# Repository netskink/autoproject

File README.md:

autoproject
===========

arduino code for triple gauge I built using arduino.
My youtube channel uploads have videos used during construction
and the final results.

http://www.youtube.com/user/netskink/videos

I gave a presentation on this project at FOSS in Raleigh and at DefCon in Las Vegas for HHV.
Here is one version of it.
https://docs.google.com/presentation/d/1aC9Kk9lGGvgu6jle9UMkTmX3eTjt8OQHqn5Oco8srgs/edit?usp=sharing

John

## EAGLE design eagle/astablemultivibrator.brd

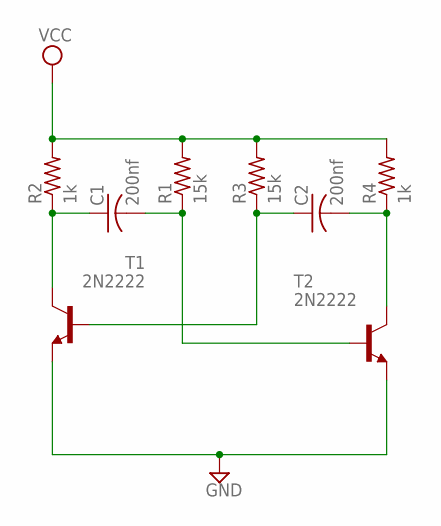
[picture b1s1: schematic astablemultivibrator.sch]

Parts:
C1, C2: 200nf; C025-030X050
R1, R3: 15k; 0309/12
R2, R4: 1k; 0309/12
T1, T2: 2N2222; TO92-EBC-OVAL

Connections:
GND: T1.E, T2.E
unnamed: C1.1, R2.1, T1.C
unnamed: C1.2, R1.1, T2.B
unnamed: C2.1, R3.1, T1.B
unnamed: C2.2, R4.1, T2.C
VCC: R1.2, R2.2, R3.2, R4.2

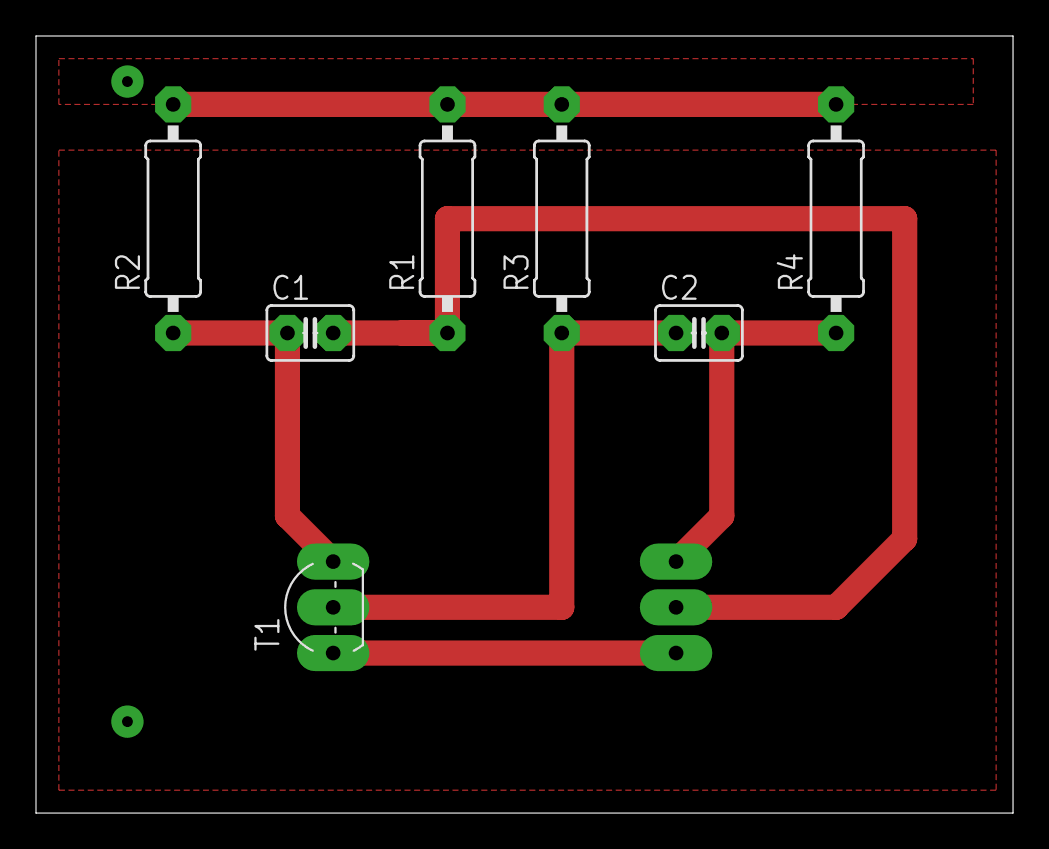
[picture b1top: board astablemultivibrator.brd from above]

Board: 2 copper layers, 54.3 x 43.2 mm, 8 parts (1 on the bottom side), 6 nets.

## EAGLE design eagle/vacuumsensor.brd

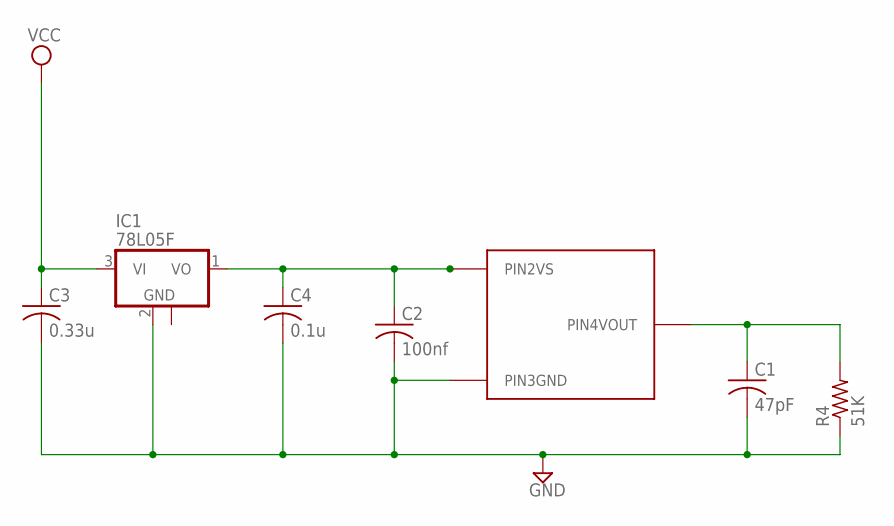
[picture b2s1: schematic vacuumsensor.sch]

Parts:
C1: 47pF; C050-024X044
C2: 100nf; C050-024X044
C3: 0.33u; C050-024X044
C4: 0.1u; C050-024X044
IC1: 78L05F; SOT89
R4: 51K; 0309/12
U$1: MPXV6115V6U; 482A

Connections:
GND: C1.2, C2.2, C3.2, C4.2, IC1.2 (GND), R4.1, U$1.P$3 (PIN3GND)
unnamed: C1.1, R4.2, U$1.P$4 (PIN4VOUT)
unnamed: C2.1, C4.1, IC1.1 (VO), U$1.P$2 (PIN2VS)
VCC: C3.1, IC1.3 (VI)

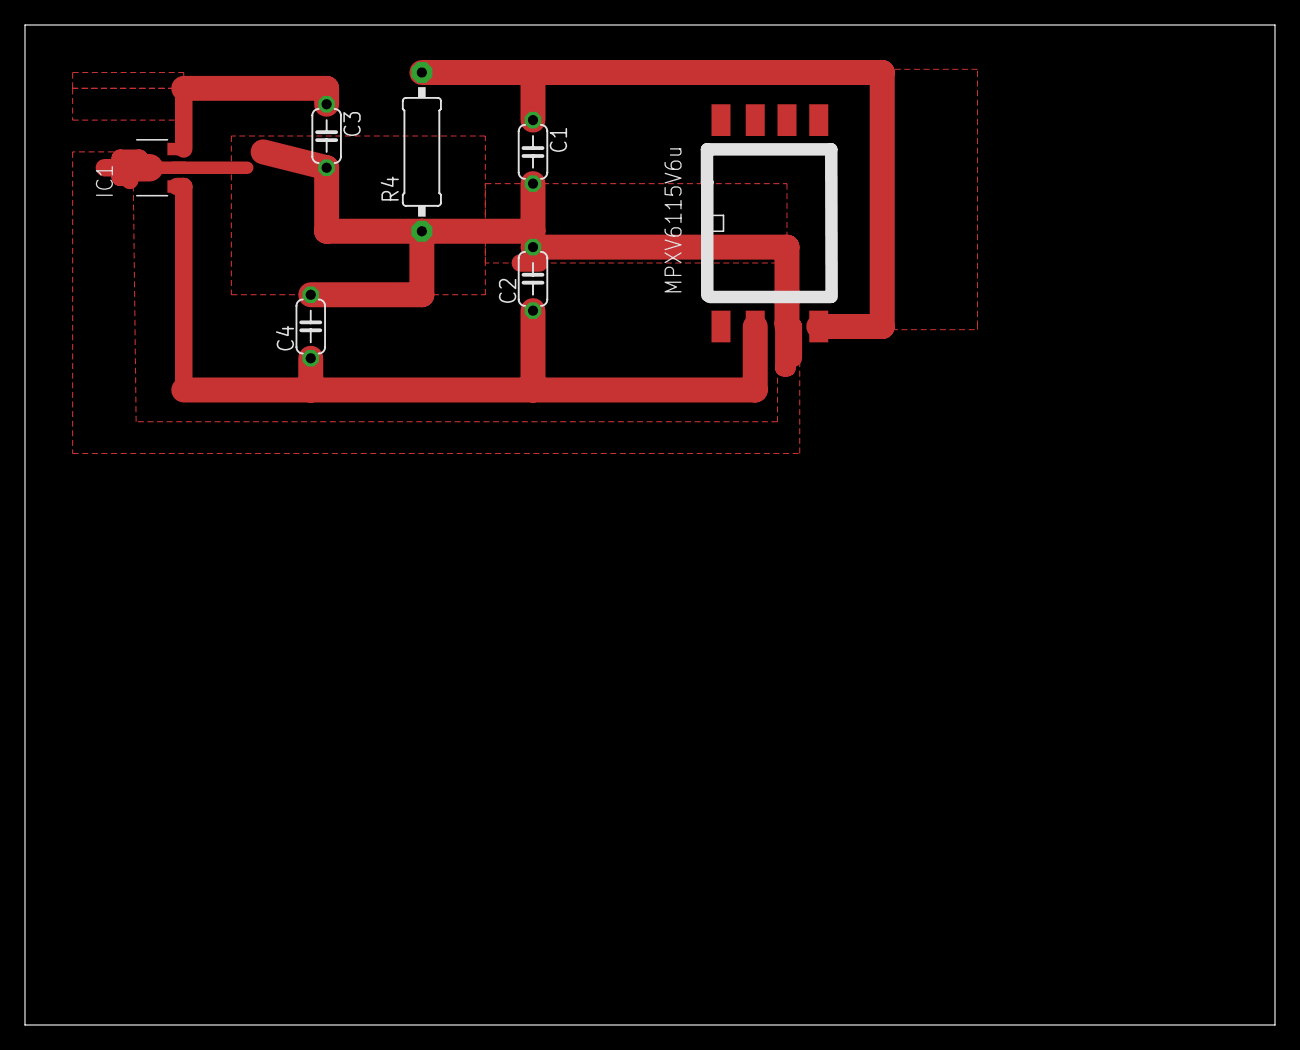
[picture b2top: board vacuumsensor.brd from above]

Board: 2 copper layers, 100.0 x 80.0 mm, 7 parts (0 on the bottom side), 4 nets.

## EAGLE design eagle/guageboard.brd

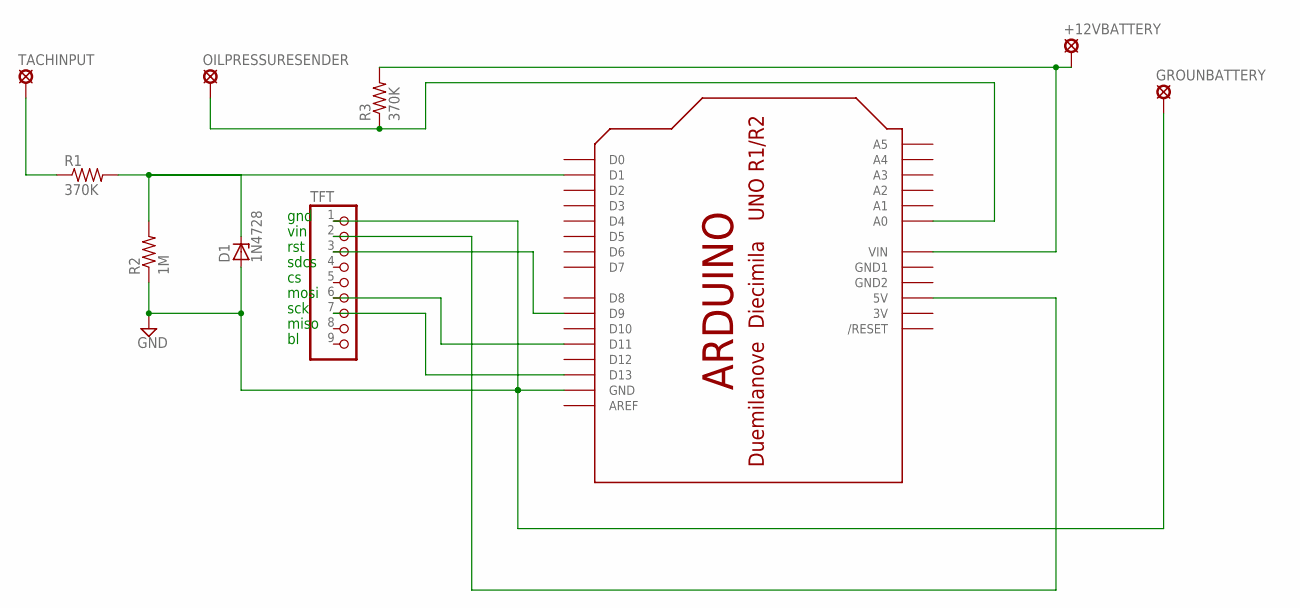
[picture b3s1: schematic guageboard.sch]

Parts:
+12VBATTERY: MCS10B
D1: 1N4728; DO41Z10
GROUNBATTERY: MCS10B
OILPRESSURESENDER: MCS10B
R1, R3: 370K; 0204/5
R2: 1M; 0204/5
TACHINPUT: MCS10B
TFT: PINHD-1X9; 1X09-BIG
U$1: ARDUINOUNO; ARDUINO

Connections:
3V: U$1.3V
5V: TFT.2, U$1.5V
GND: D1.A, GROUNBATTERY.MP, R2.1, TFT.1, U$1.GND, U$1.GND2
GND1: U$1.GND1
unnamed: D1.C, R1.2, R2.2, U$1.D1
unnamed: R1.1, TACHINPUT.MP
unnamed: OILPRESSURESENDER.MP, R3.1, U$1.A0
unnamed: TFT.7, U$1.D13
unnamed: TFT.6, U$1.D11
unnamed: TFT.3, U$1.D9
VIN: +12VBATTERY.MP, R3.2, U$1.VIN

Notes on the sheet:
gnd
vin
rst
sdcs
mosi
sck
miso

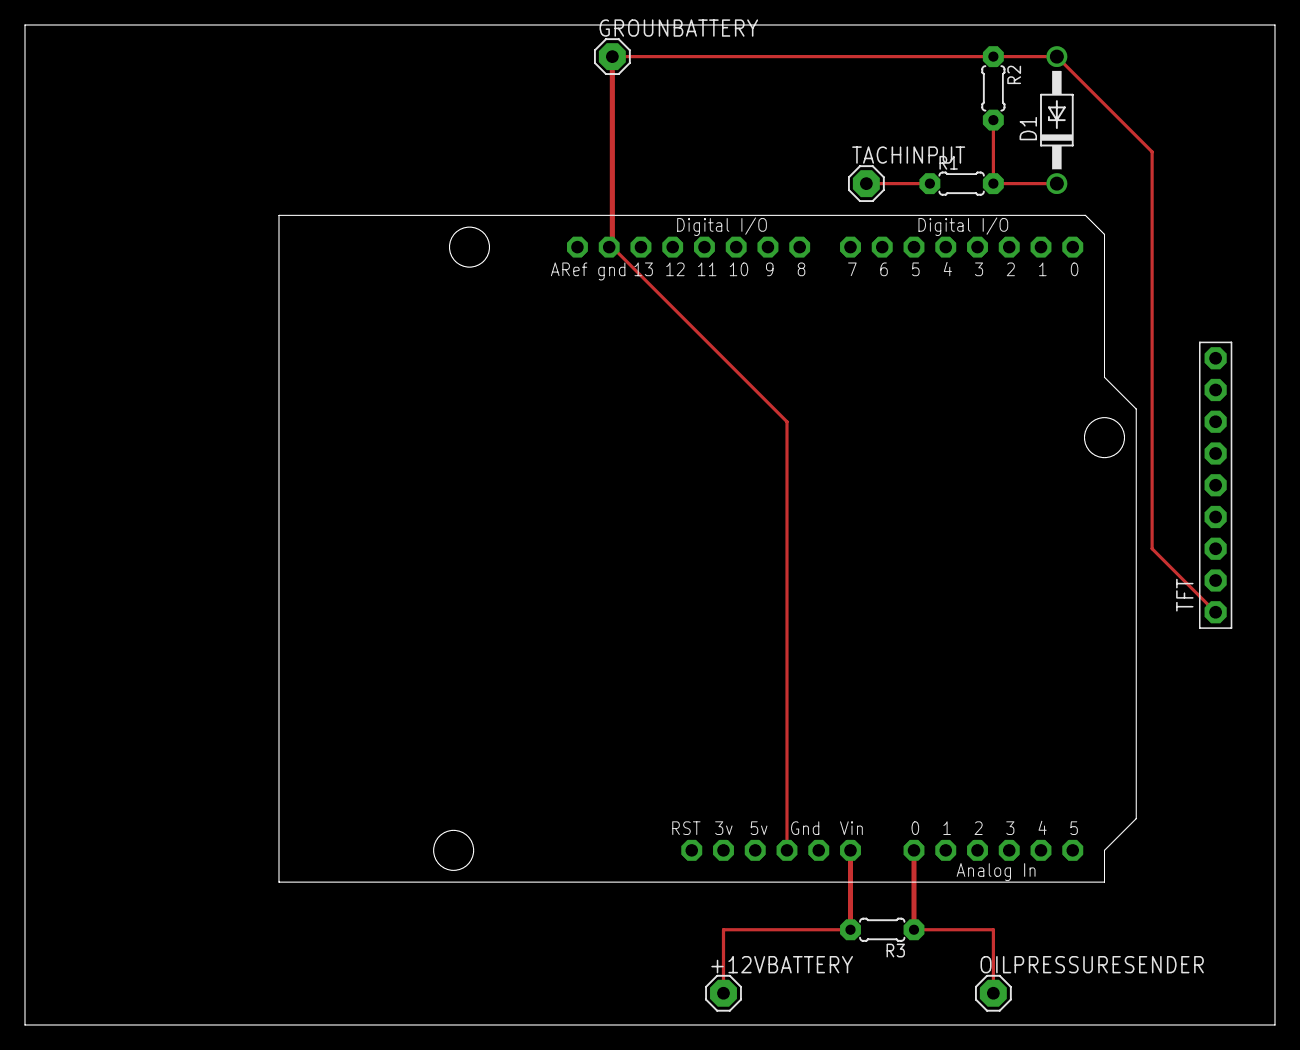
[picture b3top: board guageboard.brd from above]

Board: 2 copper layers, 100.0 x 80.0 mm, 10 parts (0 on the bottom side), 9 nets.

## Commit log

2013-05-19 readded the arduino code
2013-05-19 Added schematics
